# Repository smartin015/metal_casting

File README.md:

# metal_casting
Files infra, and automation solutions for DIY casting of exotic metals (platinum, titanium etc)

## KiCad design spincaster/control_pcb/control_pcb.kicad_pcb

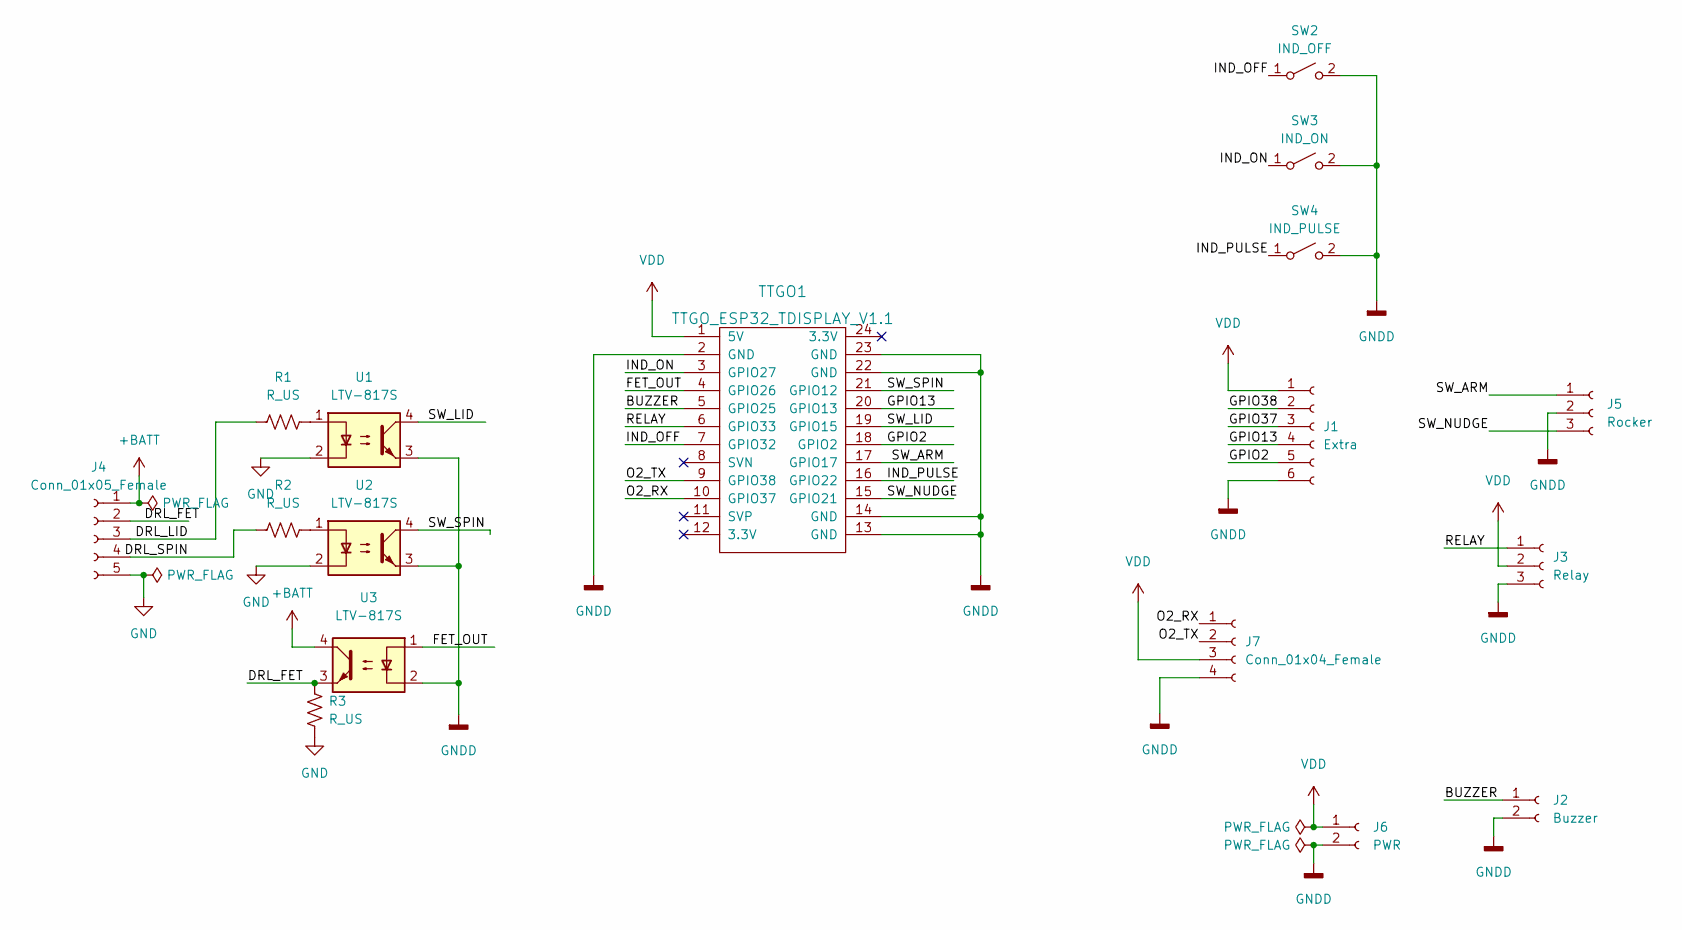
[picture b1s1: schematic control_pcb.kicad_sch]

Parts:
J1: Extra; PinHeader_1x06_P2.54mm_Vertical
J2: Buzzer; JST_PH_B2B-PH-K_1x02_P2.00mm_Vertical
J3: Relay; JST_PH_B3B-PH-K_1x03_P2.00mm_Vertical
J4: Conn_01x05_Female; Molex_KK-254_AE-6410-05A_1x05_P2.54mm_Vertical
J5: Rocker; JST_PH_B3B-PH-K_1x03_P2.00mm_Vertical
J6: PWR; JST_PH_B2B-PH-K_1x02_P2.00mm_Vertical
J7: Conn_01x04_Female; JST_PH_B4B-PH-K_1x04_P2.00mm_Vertical
R1, R2, R3: R_US; R_0805_2012Metric
SW2: IND_OFF; SW_PUSH_6mm_H5mm
SW3: IND_ON; SW_PUSH_6mm_H5mm
SW4: IND_PULSE; SW_PUSH_6mm_H5mm
TTGO1: TTGO_ESP32_TDISPLAY_V1.1; TTGO_ESP32_TDisplay_v1.1
U1, U2, U3: LTV-817S; SMDIP-4_W9.53mm

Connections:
+BATT: J4.1, U3.4
/BUZZER: J2.1, TTGO1.5 (GPIO25)
/DRL_FET: J4.2, R3.1, U3.3
/DRL_LID: J4.3, R1.1
/DRL_SPIN: J4.4, R2.1
/FET_OUT: TTGO1.4 (GPIO26), U3.1
/GPIO2: J1.5, TTGO1.18 (GPIO2)
/GPIO13: J1.4, TTGO1.20 (GPIO13)
/GPIO37: J1.3
/GPIO38: J1.2
/IND_OFF: SW2.1 (A), TTGO1.7 (GPIO32)
/IND_ON: SW3.1 (A), TTGO1.3 (GPIO27)
/IND_PULSE: SW4.1 (A), TTGO1.16 (GPIO22)
/O2_RX: J7.1, TTGO1.10 (GPIO37)
/O2_TX: J7.2, TTGO1.9 (GPIO38)
/RELAY: J3.1, TTGO1.6 (GPIO33)
/SW_ARM: J5.1, TTGO1.17 (GPIO17)
/SW_LID: TTGO1.19 (GPIO15), U1.4
/SW_NUDGE: J5.3, TTGO1.15 (GPIO21)
/SW_SPIN: TTGO1.21 (GPIO12), U2.4
GND: J4.5, R3.2, U1.2, U2.2
GNDD: J1.6, J2.2, J3.3, J5.2, J6.2, J7.4, SW2.2 (B), SW3.2 (B), SW4.2 (B), TTGO1.2 (GND), TTGO1.13 (GND), TTGO1.14 (GND), TTGO1.22 (GND), TTGO1.23 (GND), U1.3, U2.3, U3.2
unnamed: R1.2, U1.1
unnamed: R2.2, U2.1
VDD: J1.1, J3.2, J6.1, J7.3, TTGO1.1 (5V)

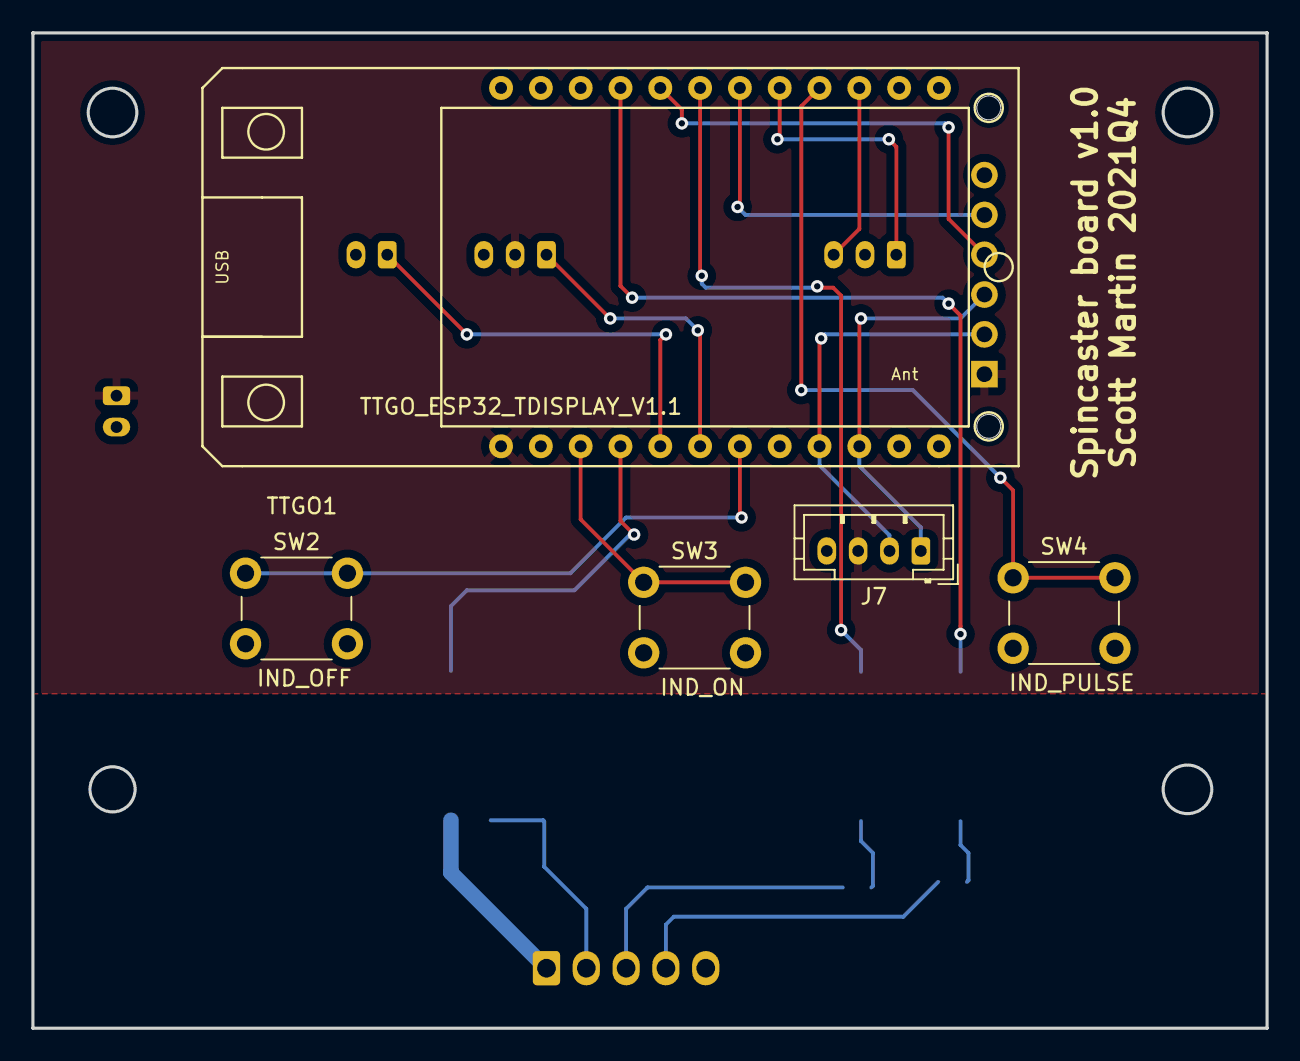
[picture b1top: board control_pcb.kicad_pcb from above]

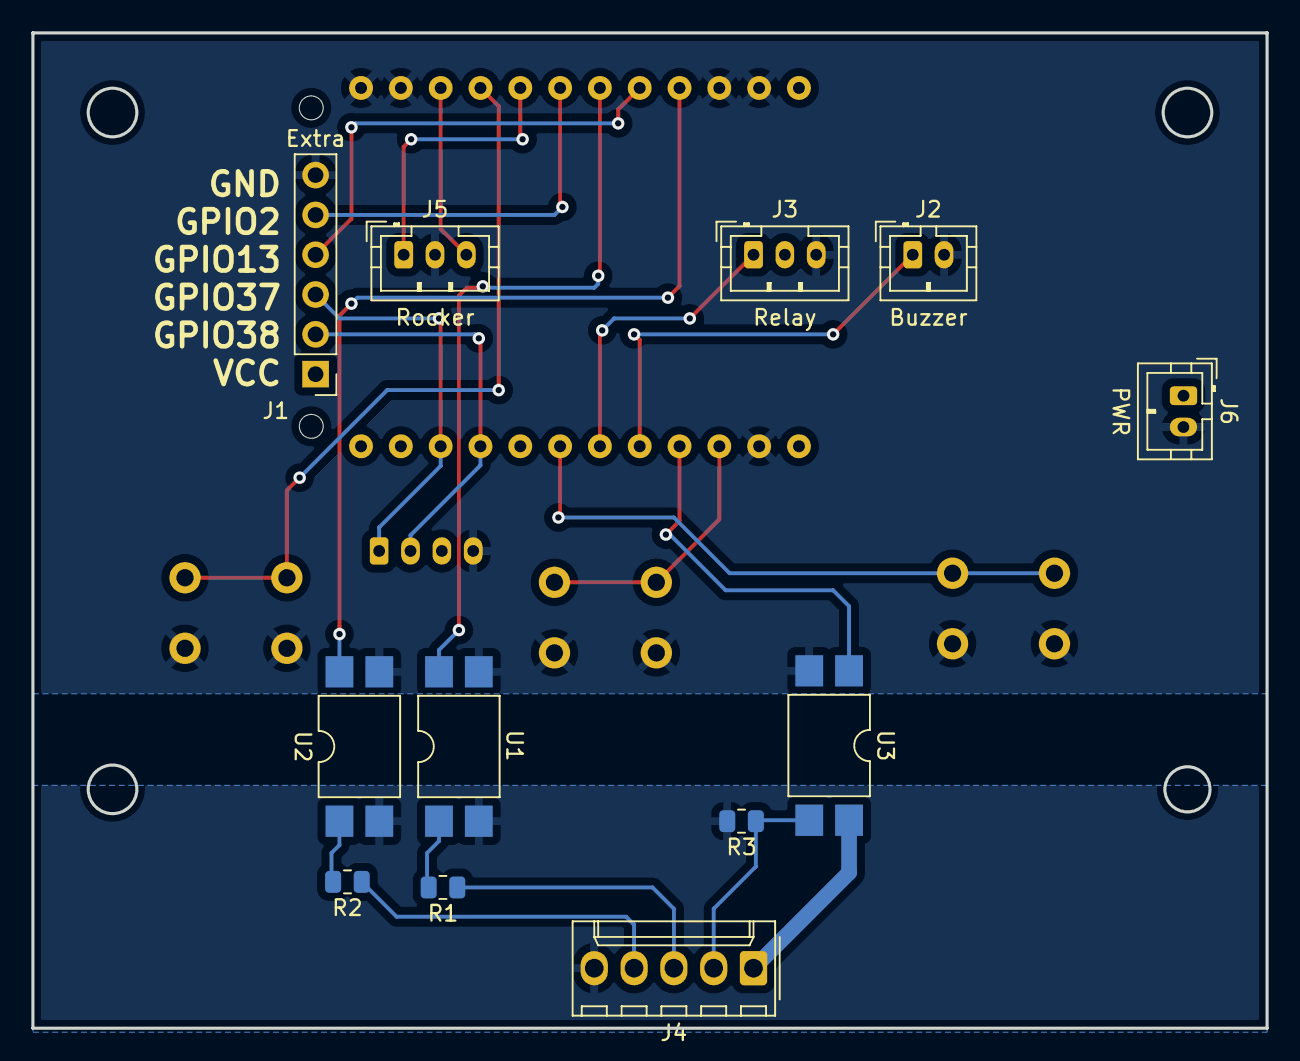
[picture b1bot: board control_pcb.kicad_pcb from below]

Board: 2 copper layers, 78.7 x 63.5 mm, 17 parts (12 on the bottom side), 23 nets.

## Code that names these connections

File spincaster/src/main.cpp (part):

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
TFT_eSPI tft = TFT_eSPI(135, 240); // Invoke custom library

#define BUZZER_PIN 25
#define BUZZER_CHANNEL 0
#define MOTOR_PIN 26
#define MOTOR_CHANNEL 1
#define INDUCTION_PIN 33

#define O2_RX 37
#define O2_TX 38

typedef enum {
  BUTTON_1,
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void buzz(int freq = 0) {
  if (freq > 0) {
    if (buzzing) {
      noTone(BUZZER_PIN, BUZZER_CHANNEL);
    }
    tone(BUZZER_PIN, freq, 0, BUZZER_CHANNEL);
    buzzing = true;
  } else {
    if (buzzing) {
      noTone(BUZZER_PIN, BUZZER_CHANNEL);
    }
    buzzing = false;
  }
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         pinMode(TFT_BL, OUTPUT); // Set backlight pin to output mode
         digitalWrite(TFT_BL, TFT_BACKLIGHT_ON); // Turn backlight on. TFT_BACKLIGHT_ON has been set in the TFT_eSPI library in the User Setup file TTGO_T_Display.h
    }
    pinMode(BUZZER_PIN, OUTPUT);
    pinMode(MOTOR_PIN, OUTPUT);
    pinMode(INDUCTION_PIN, OUTPUT);
    digitalWrite(INDUCTION_PIN, LOW);
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
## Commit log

2022-02-05 Checking in ipynb files for spincaster, also improvements to spincaster firmware
2022-04-22 Added ipynb files
2022-05-04 Add O2 sensor logic to firmware, check in control PCB kicad updates and o2 sensor mount ipynb
2022-07-02 Finished O2 sensor display and bumped spincaster FW version to v1.1
2022-10-10 Added o2 sensor test code, CLIF initial firmware
